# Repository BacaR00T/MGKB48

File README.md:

# MGKB48
Left and right part connects to the main powerboard with nice!nano (or any another pro micro pinout MCU). 

# MCU file configuration
To be able to use the nice!nano (or any other MCU with nRF52840) and KMK, it's needed to flash the MCU with [CircuitPython](https://learn.adafruit.com/welcome-to-circuitpython/installing-circuitpython) and then compile the [kmk library](https://kmkfw.io/docs/Getting_Started)

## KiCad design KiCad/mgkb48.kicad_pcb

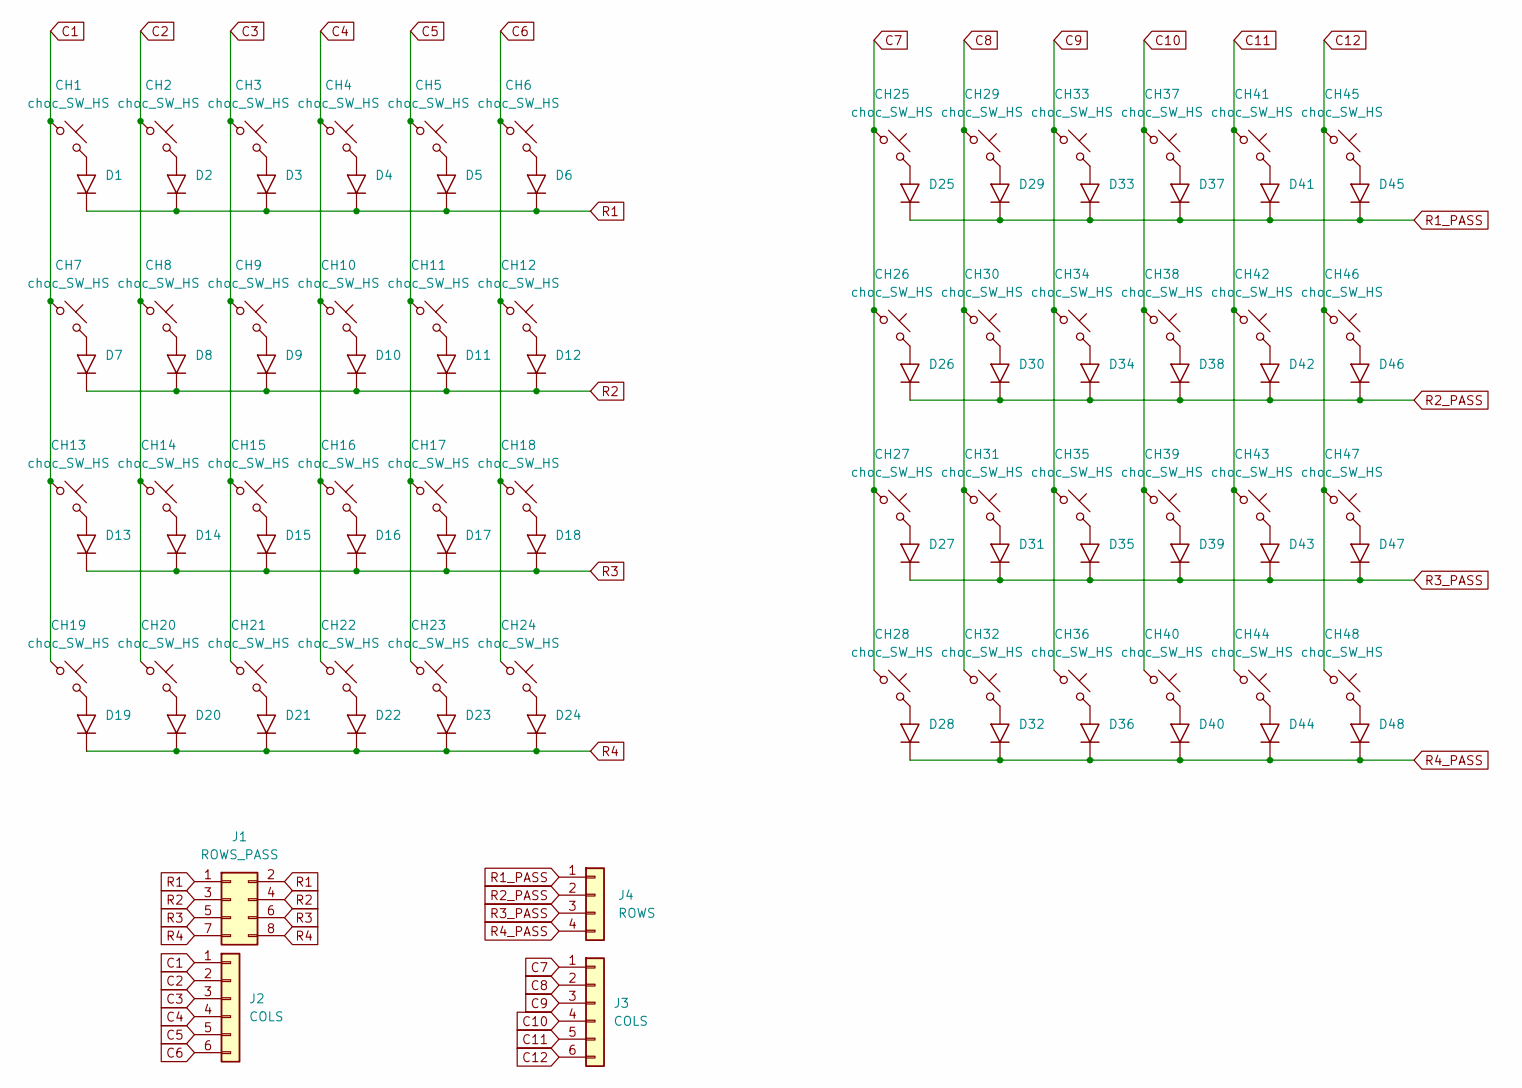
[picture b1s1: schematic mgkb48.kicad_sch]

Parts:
CH1, CH2, CH3, CH4, CH5, CH6, CH7, CH8, CH9, CH10, CH11, CH12, CH13, CH14, CH15, CH16, CH17, CH18, CH19, CH20, CH21, CH22, CH23, CH24, CH25, CH26, CH27, CH28, CH29, CH30, CH31, CH32, CH33, CH34, CH35, CH36, CH37, CH38, CH39, CH40, CH41, CH42, CH43, CH44, CH45, CH46, CH47, CH48: choc_SW_HS; SW_choc_v1_HS_1u
D1, D2, D3, D4, D5, D6, D7, D8, D9, D10, D11, D12, D13, D14, D15, D16, D17, D18, D19, D20, D21, D22, D23, D24, D25, D26, D27, D28, D29, D30, D31, D32, D33, D34, D35, D36, D37, D38, D39, D40, D41, D42, D43, D44, D45, D46, D47, D48: D_Generic; D_DO-35_P7.62mm_Horizontal
J1: ROWS_PASS; Pins_2x04_2.54mm_TH; Part Number 1-0802FBV0T
J2, J3: COLS; Pins_1x06_2.54mm_TH_SWD; Part Number 1-0601FBV0T
J4: ROWS; Pins_1x04_2.54mm_TH; Part Number 1-0401FBV0T

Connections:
C1: CH1.1, CH7.1, CH13.1, CH19.1, J2.1
C2: CH2.1, CH8.1, CH14.1, CH20.1, J2.2
C3: CH3.1, CH9.1, CH15.1, CH21.1, J2.3
C4: CH4.1, CH10.1, CH16.1, CH22.1, J2.4
C5: CH5.1, CH11.1, CH17.1, CH23.1, J2.5
C6: CH6.1, CH12.1, CH18.1, CH24.1, J2.6
C7: CH25.1, CH26.1, CH27.1, CH28.1, J3.1
C8: CH29.1, CH30.1, CH31.1, CH32.1, J3.2
C9: CH33.1, CH34.1, CH35.1, CH36.1, J3.3
C10: CH37.1, CH38.1, CH39.1, CH40.1, J3.4
C11: CH41.1, CH42.1, CH43.1, CH44.1, J3.5
C12: CH45.1, CH46.1, CH47.1, CH48.1, J3.6
unnamed: CH1.2, D1.2 (A)
unnamed: CH2.2, D2.2 (A)
unnamed: CH3.2, D3.2 (A)
unnamed: CH4.2, D4.2 (A)
unnamed: CH5.2, D5.2 (A)
unnamed: CH6.2, D6.2 (A)
unnamed: CH7.2, D7.2 (A)
unnamed: CH8.2, D8.2 (A)
unnamed: CH9.2, D9.2 (A)
unnamed: CH10.2, D10.2 (A)
unnamed: CH11.2, D11.2 (A)
unnamed: CH12.2, D12.2 (A)
unnamed: CH13.2, D13.2 (A)
unnamed: CH14.2, D14.2 (A)
unnamed: CH15.2, D15.2 (A)
unnamed: CH16.2, D16.2 (A)
unnamed: CH17.2, D17.2 (A)
unnamed: CH18.2, D18.2 (A)
unnamed: CH19.2, D19.2 (A)
unnamed: CH20.2, D20.2 (A)
unnamed: CH21.2, D21.2 (A)
unnamed: CH22.2, D22.2 (A)
unnamed: CH23.2, D23.2 (A)
unnamed: CH24.2, D24.2 (A)
unnamed: CH25.2, D25.2 (A)
unnamed: CH26.2, D26.2 (A)
unnamed: CH27.2, D27.2 (A)
unnamed: CH28.2, D28.2 (A)
unnamed: CH29.2, D29.2 (A)
unnamed: CH30.2, D30.2 (A)
unnamed: CH31.2, D31.2 (A)
unnamed: CH32.2, D32.2 (A)
unnamed: CH33.2, D33.2 (A)
unnamed: CH34.2, D34.2 (A)
unnamed: CH35.2, D35.2 (A)
unnamed: CH36.2, D36.2 (A)
unnamed: CH37.2, D37.2 (A)
unnamed: CH38.2, D38.2 (A)
unnamed: CH39.2, D39.2 (A)
unnamed: CH40.2, D40.2 (A)
unnamed: CH41.2, D41.2 (A)
unnamed: CH42.2, D42.2 (A)
unnamed: CH43.2, D43.2 (A)
unnamed: CH44.2, D44.2 (A)
unnamed: CH45.2, D45.2 (A)
unnamed: CH46.2, D46.2 (A)
unnamed: CH47.2, D47.2 (A)
unnamed: CH48.2, D48.2 (A)
R1: D1.1 (K), D2.1 (K), D3.1 (K), D4.1 (K), D5.1 (K), D6.1 (K), J1.1, J1.2
R1_PASS: D25.1 (K), D29.1 (K), D33.1 (K), D37.1 (K), D41.1 (K), D45.1 (K), J4.1
R2: D7.1 (K), D8.1 (K), D9.1 (K), D10.1 (K), D11.1 (K), D12.1 (K), J1.3, J1.4
R2_PASS: D26.1 (K), D30.1 (K), D34.1 (K), D38.1 (K), D42.1 (K), D46.1 (K), J4.2
R3: D13.1 (K), D14.1 (K), D15.1 (K), D16.1 (K), D17.1 (K), D18.1 (K), J1.5, J1.6
R3_PASS: D27.1 (K), D31.1 (K), D35.1 (K), D39.1 (K), D43.1 (K), D47.1 (K), J4.3
R4: D19.1 (K), D20.1 (K), D21.1 (K), D22.1 (K), D23.1 (K), D24.1 (K), J1.7, J1.8
R4_PASS: D28.1 (K), D32.1 (K), D36.1 (K), D40.1 (K), D44.1 (K), D48.1 (K), J4.4

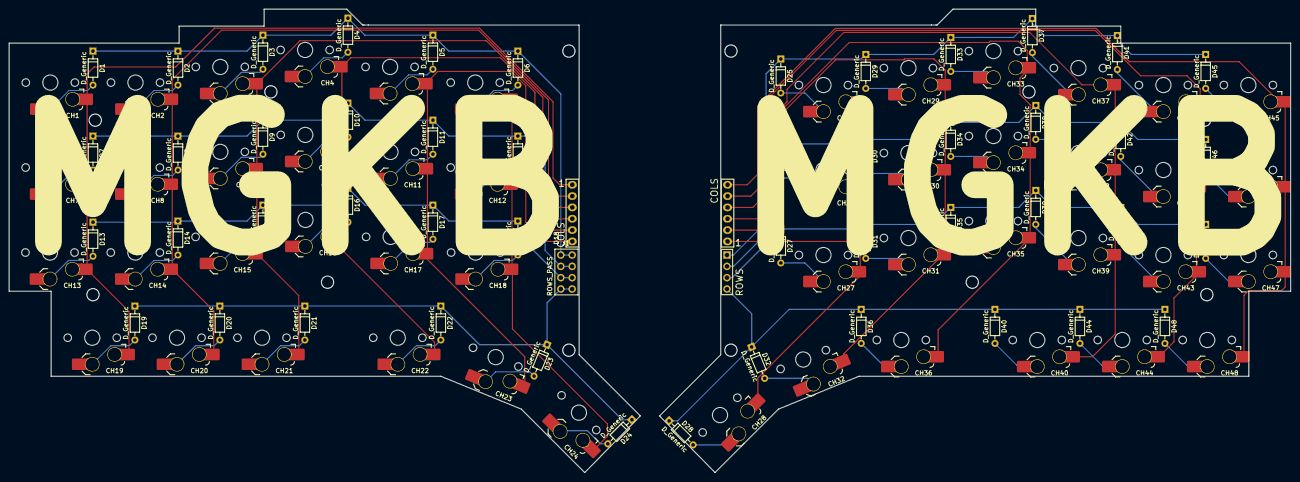
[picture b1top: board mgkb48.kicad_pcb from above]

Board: 2 copper layers, 287.3 x 103.9 mm, 100 parts (0 on the bottom side), 68 nets.

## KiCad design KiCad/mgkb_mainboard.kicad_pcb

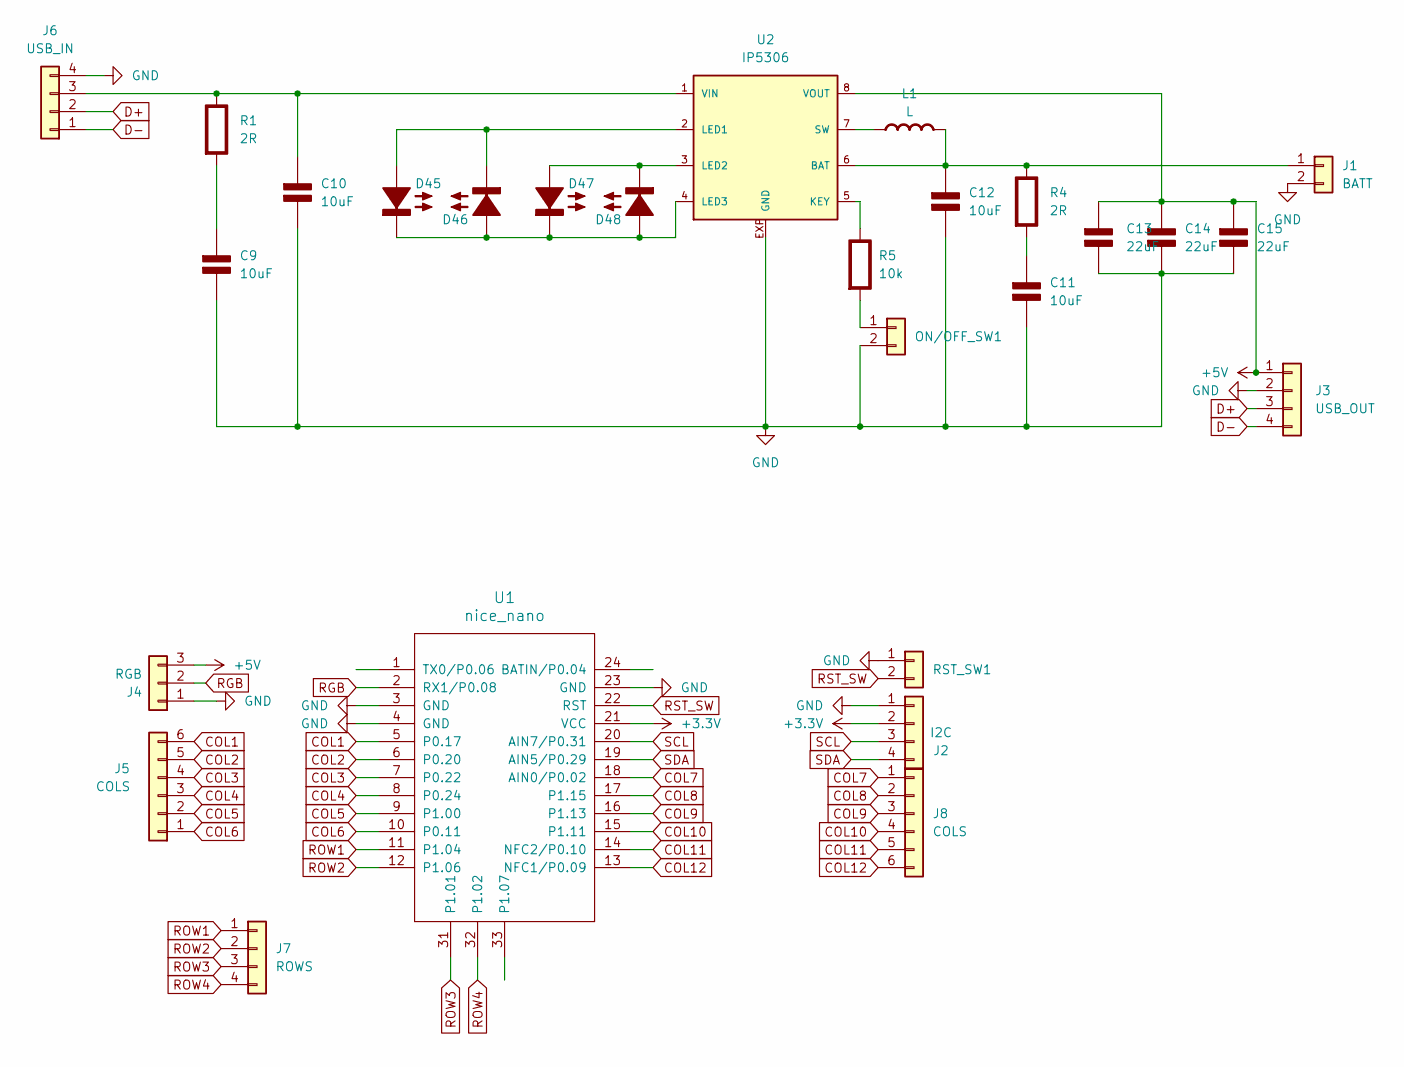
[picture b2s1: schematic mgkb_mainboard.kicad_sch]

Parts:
C9, C10, C11, C12: 10uF; C_0805; Rating V
C13, C14, C15: 22uF; C_0805; Rating V
D45, D46, D47, D48: type="" model="D-LED" lib="semiconductor.lib"; D_0805_2012Metric; Rating A
J1: BATT; Pins_1x02_2.54mm_TH; Part Number 1-0201FBV0T
J2: I2C; Pins_1x04_2.54mm_TH; Part Number 1-0401FBV0T
J3: USB_OUT; Pins_1x04_2.54mm_TH; Part Number 1-0401FBV0T
J4: RGB; Pins_1x03_2.54mm_TH; Part Number 1-0301FBV0T
J5, J8: COLS; Pins_1x06_2.54mm_TH_SWD; Part Number 1-0601FBV0T
J6: USB_IN; Pins_1x04_2.54mm_TH; Part Number 1-0401FBV0T
J7: ROWS; Pins_1x04_2.54mm_TH_SWD; Part Number 1-0401FBV0T
L1: L; L_Abracon_ASPI-0630LR; Rating A
ON/OFF_SW1: Conn_01x02; Pins_1x02_2.54mm_TH; Part Number 1-0201FBV0T
R1, R4: 2R; R_0805_2012Metric; Rating W
R5: 10k; R_0805_2012Metric; Rating W
RST_SW1: Conn_01x02; Pins_1x02_2.54mm_TH; Part Number 1-0201FBV0T
U1: nice_nano
U2: IP5306; SOP8-P

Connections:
+3V3: J2.2, U1.21 (VCC)
+5V: C13.1 (+), C14.1 (+), C15.1 (+), J3.1, J4.3, U2.8 (VOUT)
COL1: J5.6, U1.5 (P0.17)
COL2: J5.5, U1.6 (P0.20)
COL3: J5.4, U1.7 (P0.22)
COL4: J5.3, U1.8 (P0.24)
COL5: J5.2, U1.9 (P1.00)
COL6: J5.1, U1.10 (P0.11)
COL7: J8.1, U1.18 (AIN0/P0.02)
COL8: J8.2, U1.17 (P1.15)
COL9: J8.3, U1.16 (P1.13)
COL10: J8.4, U1.15 (P1.11)
COL11: J8.5, U1.14 (NFC2/P0.10)
COL12: J8.6, U1.13 (NFC1/P0.09)
D+: J3.3, J6.2
D-: J3.4, J6.1
GND: C9.2 (-), C10.2 (-), C11.2 (-), C12.2 (-), C13.2 (-), C14.2 (-), C15.2 (-), J1.2, J2.1, J3.2, J4.1, J6.4, ON/OFF_SW1.2, RST_SW1.1, U1.3 (GND), U1.4 (GND), U1.23 (GND), U2.EXP (GND)
unnamed: C9.1 (+), R1.2 (-)
unnamed: C10.1 (+), J6.3, R1.1 (+), U2.1 (VIN)
unnamed: C11.1 (+), R4.2 (-)
unnamed: C12.1 (+), J1.1, L1.2 (-), R4.1 (+), U2.6 (BAT)
unnamed: D45.2 (A+), D46.1 (K-), U2.2 (LED1)
unnamed: D45.1 (K-), D46.2 (A+), D47.1 (K-), D48.2 (A+), U2.4 (LED3)
unnamed: D47.2 (A+), D48.1 (K-), U2.3 (LED2)
unnamed: L1.1 (+), U2.7 (SW)
unnamed: ON/OFF_SW1.1, R5.2 (-)
unnamed: R5.1 (+), U2.5 (KEY)
RGB: J4.2, U1.2 (RX1/P0.08)
ROW1: J7.1, U1.11 (P1.04)
ROW2: J7.2, U1.12 (P1.06)
ROW3: J7.3, U1.31 (P1.01)
ROW4: J7.4, U1.32 (P1.02)
RST_SW: RST_SW1.2, U1.22 (RST)
SCL: J2.3, U1.20 (AIN7/P0.31)
SDA: J2.4, U1.19 (AIN5/P0.29)

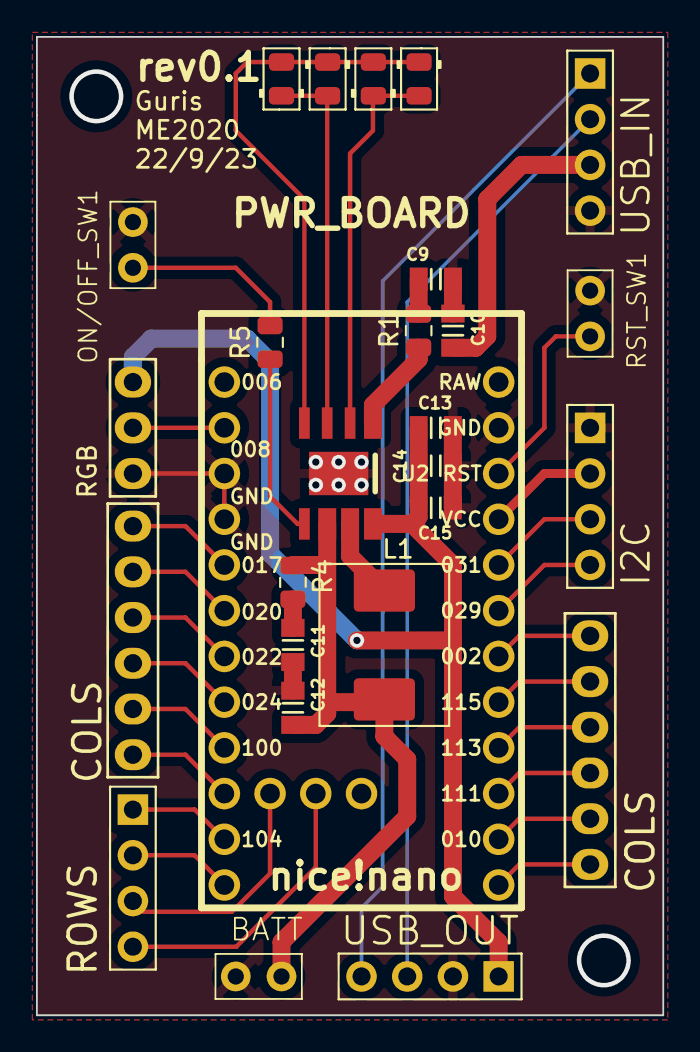
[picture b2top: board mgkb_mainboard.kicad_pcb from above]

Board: 2 copper layers, 34.8 x 54.4 mm, 27 parts (0 on the bottom side), 35 nets.

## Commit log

2023-10-07 schematics and pcb's 0.1
2023-10-27 main code
2023-10-31 Code, libs, fw
2023-11-22 STL's added
